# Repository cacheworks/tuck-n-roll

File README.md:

## tuck-n-roll

36-key split keyboard with tucky thumb encoders 

The PCB can be regenerated from the ergogen config files using;
```bash
npm install && npm run gen
```

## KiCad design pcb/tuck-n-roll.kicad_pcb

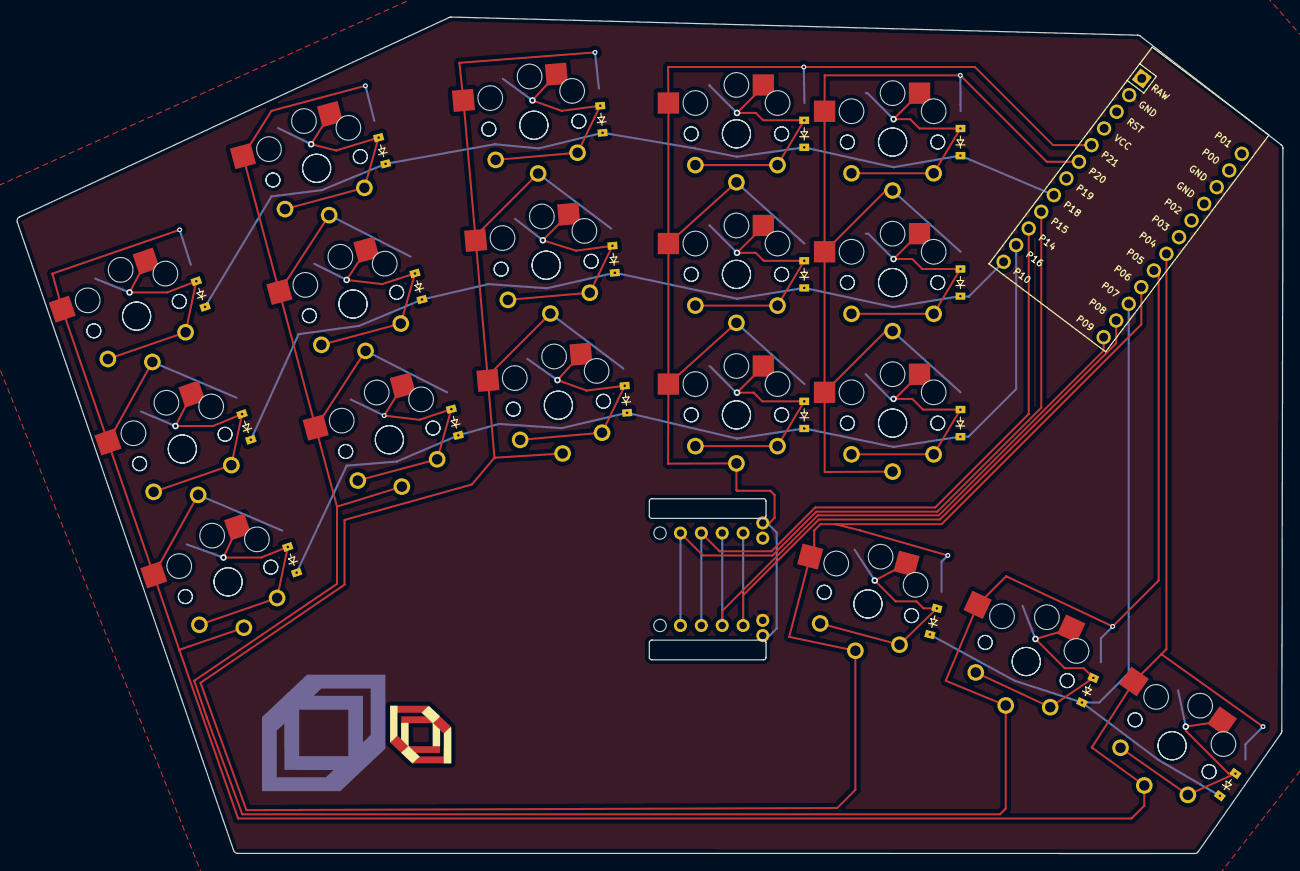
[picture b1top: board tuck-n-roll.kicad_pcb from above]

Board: 2 copper layers, 154.0 x 101.8 mm, 55 parts (0 on the bottom side), 28 nets.

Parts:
D1, D2, D3, D4, D5, D6, D7, D8, D9, D10, D11, D12, D13, D14, D15, D16, D17, D18: ComboDiode
MCU1: ProMicro
S1, S2, S3, S4, S5, S6, S7, S8, S9, S10, S11, S12, S13, S14, S15, S16, S17, S18, S19, S20, S21, S22, S23, S24, S25, S26, S27, S28, S29, S30, S31, S32, S33, S34, S35, S36: PG1350

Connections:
GND: MCU1.2, MCU1.15, MCU1.16
P4: MCU1.19, S1.2, S2.2, S3.2, S4.2, S5.2, S6.2, S35.2, S36.2
P5: MCU1.20, S7.2, S8.2, S9.2, S10.2, S11.2, S12.2, S33.2, S34.2
P6: MCU1.21, S13.2, S14.2, S15.2, S16.2, S17.2, S18.2, S31.2, S32.2
P7: D16.1, D17.1, D18.1, MCU1.22
P10: D2.1, D5.1, D8.1, D11.1, D14.1, MCU1.12
P16: D1.1, D4.1, D7.1, D10.1, D13.1, MCU1.11
P18: D3.1, D6.1, D9.1, D12.1, D15.1, MCU1.8
P20: MCU1.6, S25.2, S26.2, S27.2, S28.2, S29.2, S30.2
P21: MCU1.5, S19.2, S20.2, S21.2, S22.2, S23.2, S24.2
far_thumb: D18.2, S35.1, S36.1
home_thumb: D17.2, S33.1, S34.1
index_bottom: D10.2, S19.1, S20.1
index_home: D11.2, S21.1, S22.1
index_top: D12.2, S23.1, S24.1
inner_bottom: D13.2, S25.1, S26.1
inner_home: D14.2, S27.1, S28.1
inner_top: D15.2, S29.1, S30.1
middle_bottom: D7.2, S13.1, S14.1
middle_home: D8.2, S15.1, S16.1
middle_top: D9.2, S17.1, S18.1
near_thumb: D16.2, S31.1, S32.1
pinky_bottom: D1.2, S1.1, S2.1
pinky_home: D2.2, S3.1, S4.1
pinky_top: D3.2, S5.1, S6.1
ring_bottom: D4.2, S7.1, S8.1
ring_home: D5.2, S9.1, S10.1
ring_top: D6.2, S11.1, S12.1

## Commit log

2021-11-21 Add package.json, update README.md
2021-11-23 Update YAML to latest rev
2021-11-25 Add photo
2022-01-26 Clean up / comment ergogen config
2022-10-21 Remove column_mark property to avoid confusion, comment custom params
2022-10-21 Add more columns about the matrix pin assignment
